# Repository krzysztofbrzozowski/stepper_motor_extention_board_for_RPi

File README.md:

# Stepper motor extention board for Raspberry Pi

Simple extension board for controlling stepper motors (up to 3). Board contains Li-Po battery controller (2-4s). It is also possible to charge battery via USB C. Basic firmware you can find here [stepper_motor_extention_board_firmware.git](https://github.com/krzysztofbrzozowski/stepper_motor_extention_board_firmware.git).
Controller is using simple algorithm for controlling ttepper motors [packets table](https://krzysztofbrzozowski.pl/media/2020/04/05/packet_encoding.png).

Whole project is describerd in polish on my webpage: https://krzysztofbrzozowski.pl/projekt/steronik-silnikow-krokowych-rpi-kontroler-aku-usbc/

## Repository Contents

- **/PCB** - Eagle PCB and schematic files, schematic in PDF

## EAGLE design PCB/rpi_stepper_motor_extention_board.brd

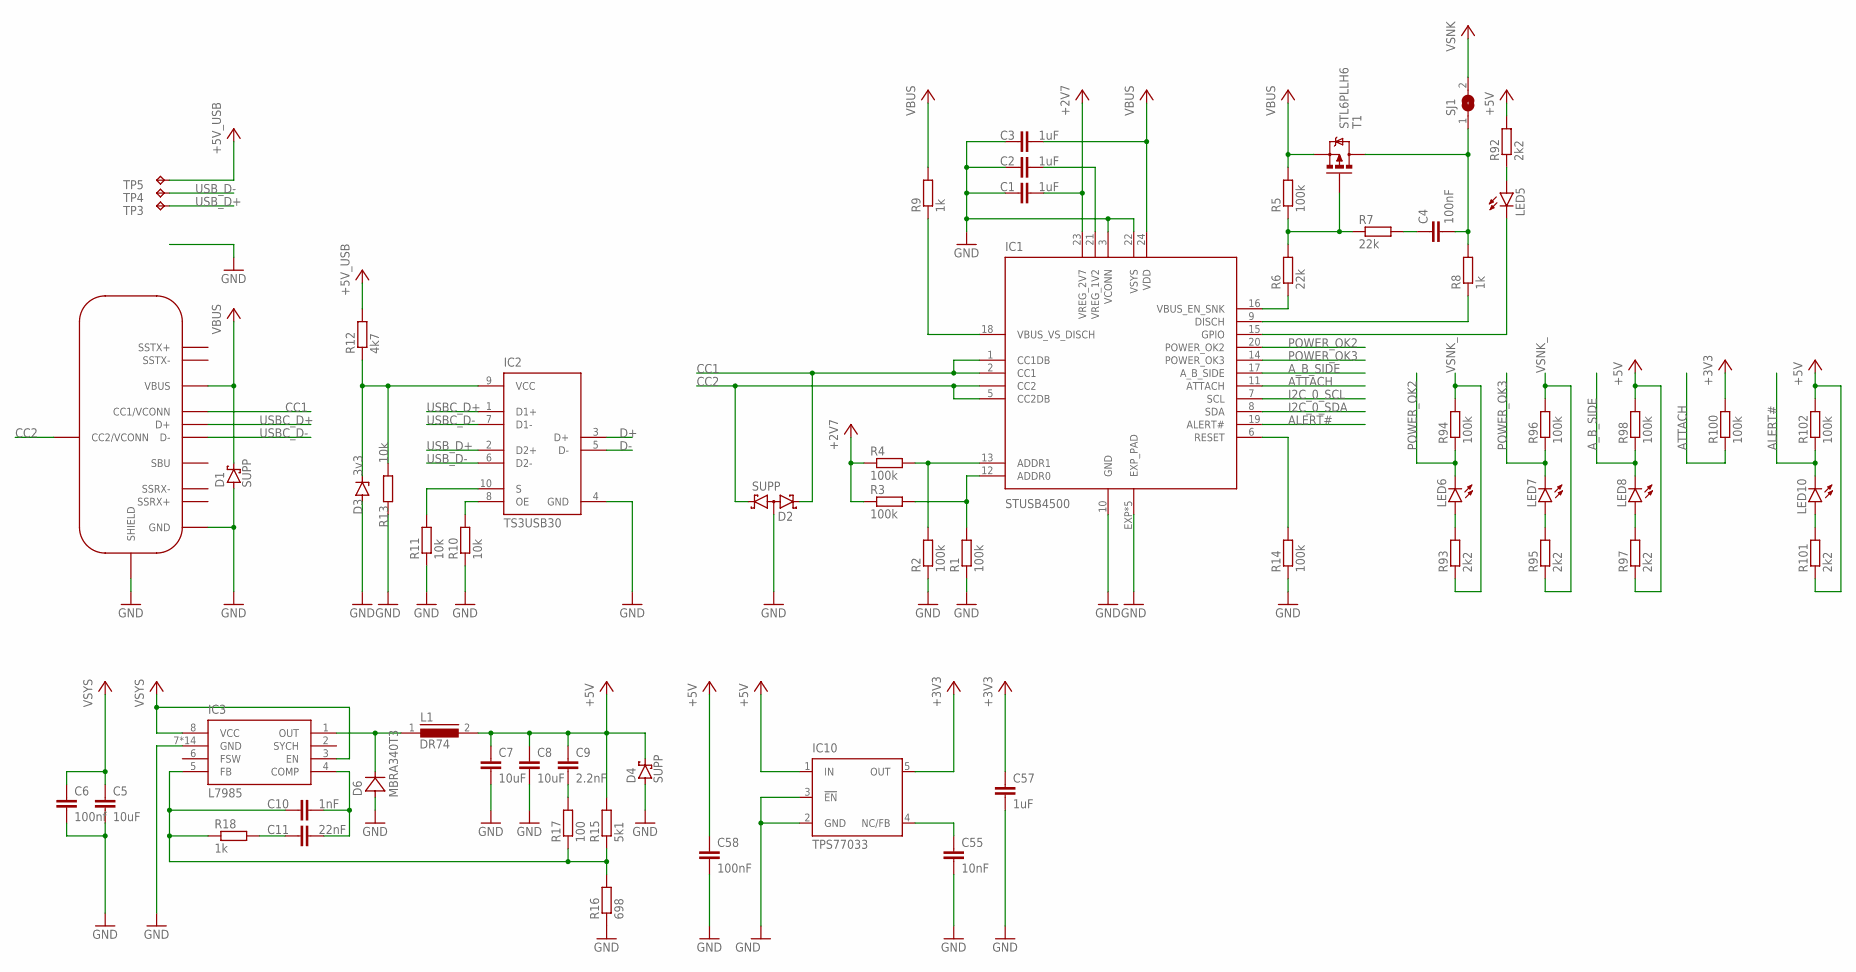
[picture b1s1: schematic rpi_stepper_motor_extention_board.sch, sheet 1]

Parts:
C1, C2, C57: 1uF; C0402K
C3: 1uF; C0603
C4, C58: 100nF; C0402K
C5: 10uF; C1206K
C6: 100nf; C0402K
C7, C8: 10uF; C1210
C9: 2.2nF; C0402K
C10: 1nF; C0402K
C11: 22nF; C0402K
C55: 10nF; C0402K
CON1: USB-TYPE-CHYBRID; USB-TYPE-C-HYBRID
D1, D4: SUPP; SOD123FL
D2: SUPP; SOT23
D3: 3v3; SOD80C
D6: MBRA340T3; SMA
IC1: STUSB4500; QFN50P400X400X90-25T270
IC2: TS3USB30; QFN40P180X145X55-10
IC3: L7985; SOIC127P600X170-8
IC10: TPS77033; SOT23-DBV
L1: DR74
LED5, LED6, LED7, LED8, LED10: LEDCHIPLED_0603; CHIPLED_0603
R1, R2, R3, R4, R5, R14, R94, R96, R98, R100, R102: 100k; R0402
R6, R7: 22k; R0402
R8, R9: 1k; R0603
R10, R11, R13: 10k; R0402
R12: 4k7; R0402
R15: 5k1; R0805
R16: 698; R0805
R17: 100; R0402
R18: 1k; R0402
R92, R93, R95, R97, R101: 2k2; R0402
SJ1: SJ
T1: STL6PLLH6; POWERPAK1212-8
TP3, TP4, TP5: TPB1,27; B1,27

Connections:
+2V7: C1.2, IC1.23 (VREG_2V7), R3.1, R4.1
+3V3: C57.1, IC10.5 (OUT), R100.2; also elsewhere on the board
+5V: C7.1, C8.1, C9.1, C58.1, D4.C, IC10.1 (IN), L1.2, R15.2, R92.2, R97.1, R98.2, R101.1, R102.2; also elsewhere on the board
+5V_USB: R12.2, TP5.TP
ALERT#: IC1.19 (ALERT#), LED10.C, R102.1
ATTACH: IC1.11 (ATTACH), R100.1; also elsewhere on the board
A_B_SIDE: IC1.17 (A_B_SIDE), LED8.C, R98.1
CC1: CON1.5 (CC1/VCONN), D2.2 (K2), IC1.1 (CC1DB), IC1.2 (CC1)
CC2: CON1.B5 (CC2/VCONN), D2.1 (K1), IC1.4 (CC2), IC1.5 (CC2DB)
D+: IC2.3 (D+); also elsewhere on the board
D-: IC2.5 (D-); also elsewhere on the board
GND: C1.1, C2.1, C3.1, C5.2, C6.2, C7.2, C8.2, C55.2, C57.2, C58.2, CON1.1 (GND), CON1.12 (GND), CON1.B1 (GND), CON1.B12 (GND), CON1.P$1 (SHIELD), CON1.P$2 (SHIELD), CON1.P$3 (SHIELD), CON1.P$4 (SHIELD), CON1.P$7 (SHIELD), CON1.P$8 (SHIELD), CON1.P$9 (SHIELD), CON1.P$10 (SHIELD), CON1.P$11 (SHIELD), CON1.P$12 (SHIELD), CON1.P$13 (SHIELD), CON1.P$14 (SHIELD), CON1.P$15 (SHIELD), CON1.P$16 (SHIELD), CON1.P$17 (SHIELD), CON1.P$18 (SHIELD), CON1.P$19 (SHIELD), CON1.P$20 (SHIELD), CON1.P$21 (SHIELD), CON1.P$22 (SHIELD), CON1.P$23 (SHIELD), CON1.P$24 (SHIELD), CON1.P$25 (SHIELD), CON1.P$26 (SHIELD), CON1.P$27 (SHIELD), CON1.P$28 (SHIELD), CON1.P$29 (SHIELD), CON1.P$30 (SHIELD), CON1.P$31 (SHIELD), CON1.P$32 (SHIELD), CON1.P$33 (SHIELD), CON1.P$34 (SHIELD), CON1.P$35 (SHIELD), D1.A, D2.3 (AA), D3.A, D4.A, D6.A, IC1.3 (VCONN), IC1.10 (GND), IC1.22 (VSYS), IC1.EXP (EXP_PAD), IC1.P$1 (EXP_PAD), IC1.P$2 (EXP_PAD), IC1.P$3 (EXP_PAD), IC1.P$4 (EXP_PAD), IC2.4 (GND), IC3.7 (GND), IC3.EXP (GND), IC3.P$1 (GND), IC3.P$2 (GND), IC3.P$3 (GND), IC3.P$4 (GND), IC3.P$5 (GND), IC3.P$6 (GND), IC3.P$7 (GND), IC3.P$8 (GND), IC3.P$9 (GND), IC3.P$10 (GND), IC3.P$11 (GND), IC3.P$12 (GND), IC10.2 (GND), IC10.3 (!EN), R1.1, R2.1, R10.1, R11.1, R13.2, R14.1, R16.1; also elsewhere on the board
I2C_0_SCL: IC1.7 (SCL); also elsewhere on the board
I2C_0_SDA: IC1.8 (SDA); also elsewhere on the board
unnamed: IC1.12 (ADDR0), R1.2, R3.2
unnamed: IC1.13 (ADDR1), R2.2, R4.2
unnamed: C2.2, IC1.21 (VREG_1V2)
unnamed: C4.1, R7.2
unnamed: IC1.16 (VBUS_EN_SNK), R6.1
unnamed: R5.1, R6.2, R7.1, T1.G
unnamed: IC1.18 (VBUS_VS_DISCH), R9.1
unnamed: IC1.9 (DISCH), R8.1
unnamed: IC2.8 (OE), R10.2
unnamed: IC2.10 (S), R11.2
unnamed: D6.C, IC3.1 (OUT), L1.1
unnamed: D3.C, IC2.9 (VCC), R12.1, R13.1
unnamed: IC1.6 (RESET), R14.2
unnamed: C10.1, IC3.5 (FB), R15.1, R16.2, R17.1, R18.1
unnamed: C9.2, R17.2
unnamed: C10.2, C11.2, IC3.4 (COMP)
unnamed: C11.1, R18.2
unnamed: C55.1, IC10.4 (NC/FB)
unnamed: LED5.A, R92.1
unnamed: LED6.A, R93.2
unnamed: LED10.A, R101.2
unnamed: LED7.A, R95.2
unnamed: IC1.15 (GPIO), LED5.C
unnamed: LED8.A, R97.2
POWER_OK2: IC1.20 (POWER_OK2), LED6.C, R94.1
POWER_OK3: IC1.14 (POWER_OK3), LED7.C, R96.1
USBC_D+: CON1.6 (D+), CON1.B6 (D+), IC2.1 (D1+)
USBC_D-: CON1.7 (D-), CON1.B7 (D-), IC2.7 (D1-)
USB_D+: IC2.2 (D2+), TP3.TP
USB_D-: IC2.6 (D2-), TP4.TP
VBUS: C3.2, CON1.4 (VBUS), CON1.9 (VBUS), CON1.B4 (VBUS), CON1.B9 (VBUS), D1.C, IC1.24 (VDD), R5.2, R9.2, T1.S1 (S), T1.S2 (S), T1.S3 (S)
VSNK: SJ1.2; also elsewhere on the board
VSNK_: C4.2, R8.2, R93.1, R94.2, R95.1, R96.2, SJ1.1, T1.D1 (D), T1.D2 (D), T1.D3 (D), T1.D4 (D), T1.DPAD (D)
VSYS: C5.1, C6.1, IC3.3 (EN), IC3.8 (VCC); also elsewhere on the board

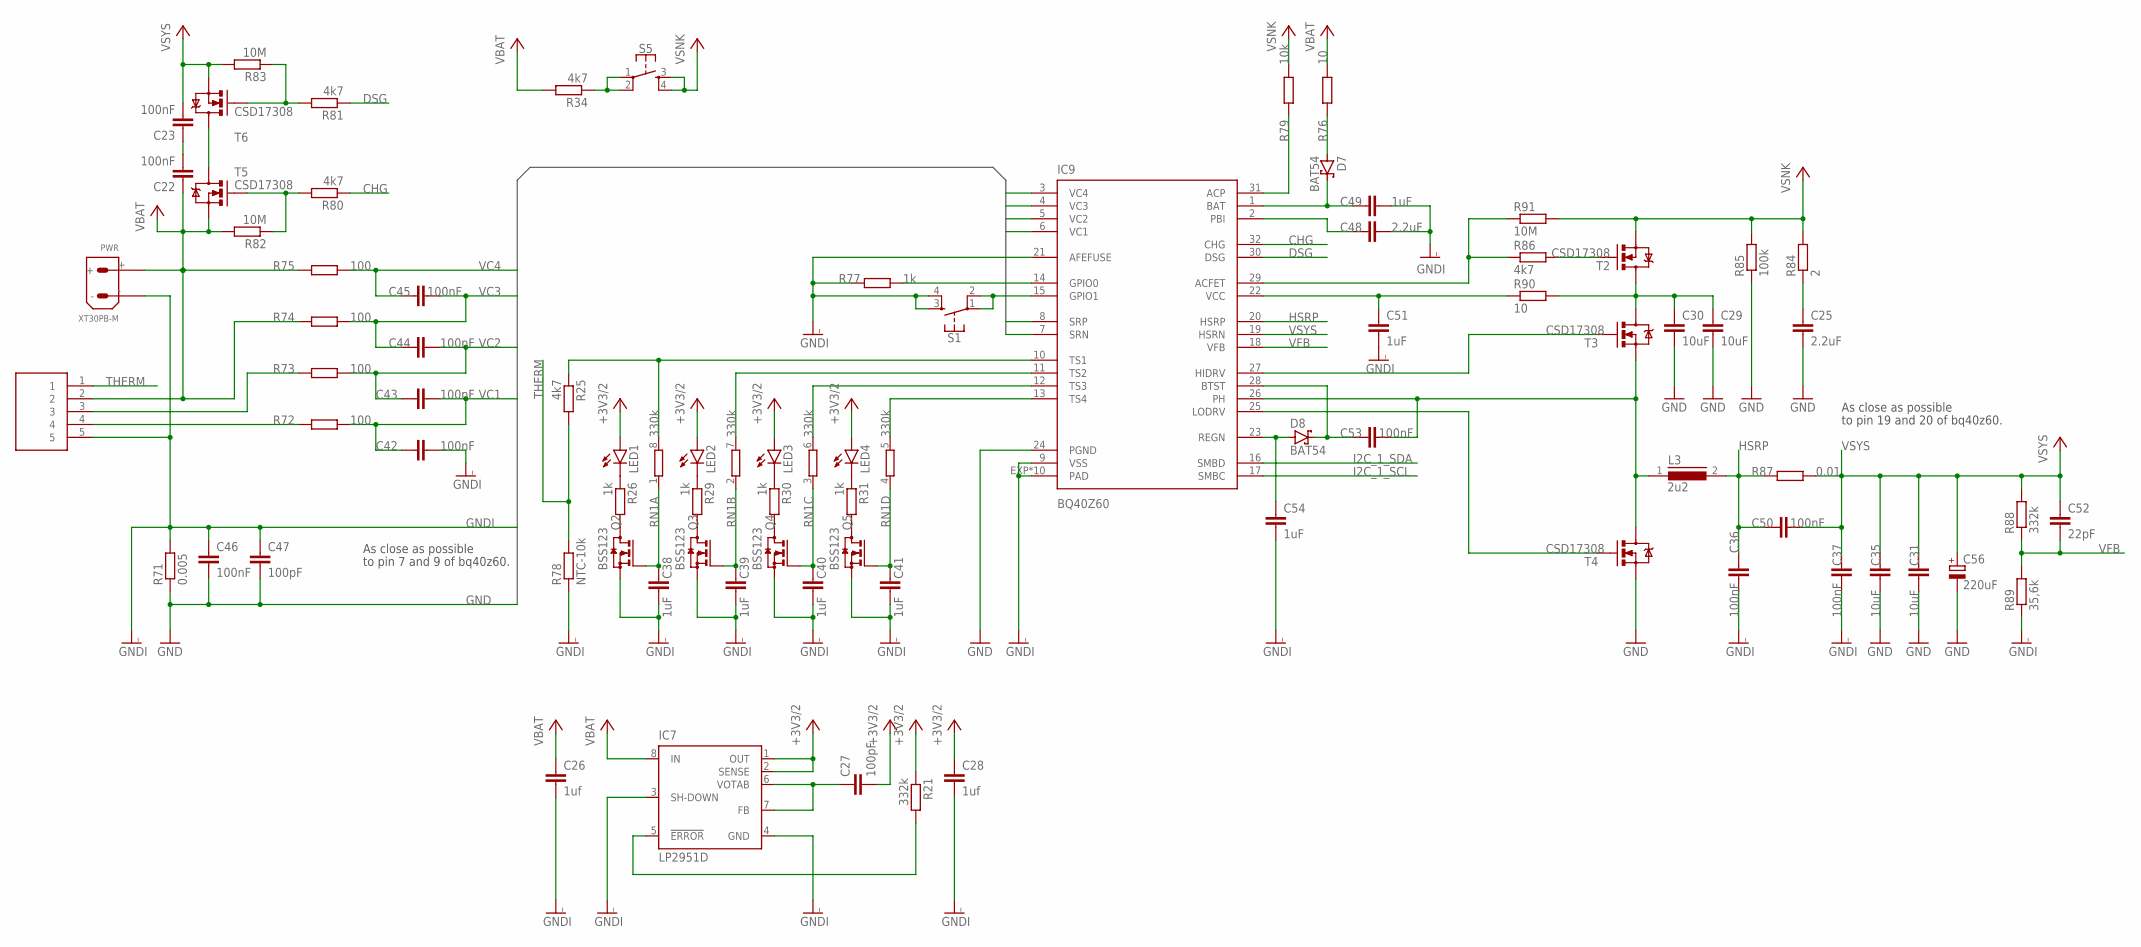
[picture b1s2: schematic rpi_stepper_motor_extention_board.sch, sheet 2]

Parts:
C22, C23: 100nF; C0603K
C25, C48: 2.2uF; C0603K
C26, C28: 1uf; C0402
C27, C47: 100pF; C0402
C29, C30, C31, C35: 10uF; C1206K
C36, C37, C42, C43, C44, C45, C50, C53: 100nF; C0402K
C38, C39, C40, C41: 1uF; C0402K
C46: 100nF; C0402
C49, C51, C54: 1uF; C0603K
C52: 22pF; C0402K
C56: 220uF; 153CLV-0605
D7, D8: BAT54; SOD123FL
IC7: LP2951D; SO08
IC9: BQ40Z60; QFN50P500X500X100-33T345
L3: 2u2; DR74
LED1, LED2, LED3, LED4: LEDCHIPLED_0603; CHIPLED_0603
PWR: XT30PB-M
Q2, Q3, Q4, Q5: BSS123; SOT23
R21: 332k; R0402
R25, R34, R80, R81, R86: 4k7; R0402
R26, R29, R30, R31, R77: 1k; R0402
R71: 0.005; R2010
R72, R73, R74, R75: 100; R0603
R76: 10; R0402
R78: NTC-10k; R0603
R79: 10k; R0402
R82, R83, R91: 10M; R0402
R84: 2; R0603
R85: 100k; R0402
R87: 0.01; R2512
R88: 332k; R0805
R89: 35,6k; R0805
R90: 10; R1206
RN1: 330k; 0603-ARC
S1, S5: MOMENTARY-SWITCH-SPST-2-SMD-4.6X2.8MM; TACTILE_SWITCH_SMD_4.6X2.8MM
T2, T3, T4, T5, T6: CSD17308; POWERPAK1212-8
U$1: 5PIN_CON_JOINT_TECH

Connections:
+3V3/2: C27.2, C28.1, IC7.1 (OUT), IC7.2 (SENSE), LED1.A, LED2.A, LED3.A, LED4.A, R21.1
CHG: IC9.32 (CHG), R80.1
DSG: IC9.30 (DSG), R81.1
GND: C25.2, C29.2, C30.2, C31.2, C35.2, C46.2, C47.2, C56.-, IC9.7 (SRN), IC9.24 (PGND), R71.1, R85.1, T4.S1 (S), T4.S2 (S), T4.S3 (S); also elsewhere on the board
GNDI: C26.2, C28.2, C36.2, C37.2, C38.2, C39.2, C40.2, C41.2, C42.1, C46.1, C47.1, C48.2, C49.2, C51.2, C54.2, IC7.3 (SH-DOWN), IC7.4 (GND), IC9.8 (SRP), IC9.9 (VSS), IC9.21 (AFEFUSE), IC9.EXP (PAD), IC9.P$1 (PAD), IC9.P$2 (PAD), IC9.P$3 (PAD), IC9.P$4 (PAD), IC9.P$5 (PAD), IC9.P$6 (PAD), IC9.P$7 (PAD), IC9.P$8 (PAD), IC9.P$9 (PAD), PWR.-, Q2.2 (S), Q3.2 (S), Q4.2 (S), Q5.2 (S), R71.2, R77.1, R78.1, R89.1, S1.3, S1.4, U$1.5
HSRP: C36.1, C50.1, IC9.20 (HSRP), L3.2, R87.1
I2C_1_SCL: IC9.17 (SMBC); also elsewhere on the board
I2C_1_SDA: IC9.16 (SMBD); also elsewhere on the board
unnamed: LED1.C, R26.1
unnamed: LED2.C, R29.1
unnamed: LED3.C, R30.1
unnamed: LED4.C, R31.1
unnamed: C27.1, IC7.6 (VOTAB), IC7.7 (FB)
unnamed: Q2.3 (D), R26.2
unnamed: Q3.3 (D), R29.2
unnamed: IC7.5 (!ERROR), R21.2
unnamed: Q5.3 (D), R31.2
unnamed: Q4.3 (D), R30.2
unnamed: R34.1, S5.1, S5.2
unnamed: C38.1, Q2.1 (G), RN1.1
unnamed: C48.1, IC9.2 (PBI)
unnamed: IC9.10 (TS1), R25.1, RN1.8 (2)
unnamed: IC9.11 (TS2), RN1.7 (2)
unnamed: IC9.12 (TS3), RN1.6 (2)
unnamed: IC9.13 (TS4), RN1.5 (2)
unnamed: C39.1, Q3.1 (G), RN1.2 (1)
unnamed: D7.A, R76.1
unnamed: R72.1, U$1.4
unnamed: C40.1, Q4.1 (G), RN1.3 (1)
unnamed: C41.1, Q5.1 (G), RN1.4 (1)
unnamed: C49.1, D7.C, IC9.1 (BAT)
unnamed: R73.1, U$1.3
unnamed: IC9.14 (GPIO0), R77.2
unnamed: IC9.15 (GPIO1), S1.1, S1.2
unnamed: IC9.31 (ACP), R79.1
unnamed: T5.D1 (D), T5.D2 (D), T5.D3 (D), T5.D4 (D), T5.DPAD (D), T6.D1 (D), T6.D2 (D), T6.D3 (D), T6.D4 (D), T6.DPAD (D)
unnamed: R80.2, R82.1, T5.G
unnamed: R81.2, R83.1, T6.G
unnamed: C25.1, R84.1
unnamed: C22.2, C23.1
unnamed: C29.1, C30.1, R90.2, T2.D1 (D), T2.D2 (D), T2.D3 (D), T2.D4 (D), T2.DPAD (D), T3.D1 (D), T3.D2 (D), T3.D3 (D), T3.D4 (D), T3.DPAD (D)
unnamed: C53.2, IC9.26 (PH), L3.1, T3.S1 (S), T3.S2 (S), T3.S3 (S), T4.D1 (D), T4.D2 (D), T4.D3 (D), T4.D4 (D), T4.DPAD (D)
unnamed: R86.2, T2.G
unnamed: IC9.27 (HIDRV), T3.G
unnamed: IC9.25 (LODRV), T4.G
unnamed: IC9.29 (ACFET), R86.1, R91.1
unnamed: C51.1, IC9.22 (VCC), R90.1
unnamed: C54.1, D8.A, IC9.23 (REGN)
unnamed: C53.1, D8.C, IC9.28 (BTST)
THERM: R25.2, R78.2, U$1.1
VBAT: C22.1, C26.1, IC7.8 (IN), PWR.+, R34.2, R74.1, R75.1, R76.2, R82.2, T5.S1 (S), T5.S2 (S), T5.S3 (S), U$1.2
VC1: C42.2, C43.1, IC9.6 (VC1), R72.2
VC2: C43.2, C44.1, IC9.5 (VC2), R73.2
VC3: C44.2, C45.1, IC9.4 (VC3), R74.2
VC4: C45.2, IC9.3 (VC4), R75.2
VFB: C52.2, IC9.18 (VFB), R88.1, R89.2
VSNK: R79.2, R84.2, R85.2, R91.2, S5.3, S5.4, T2.S1 (S), T2.S2 (S), T2.S3 (S); also elsewhere on the board
VSYS: C23.2, C31.1, C35.1, C37.1, C50.2, C52.1, C56.+, IC9.19 (HSRN), R83.2, R87.2, R88.2, T6.S1 (S), T6.S2 (S), T6.S3 (S); also elsewhere on the board

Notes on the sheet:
As close as possible
to pin 7 and 9 of bq40z60.
to pin 19 and 20 of bq40z60.

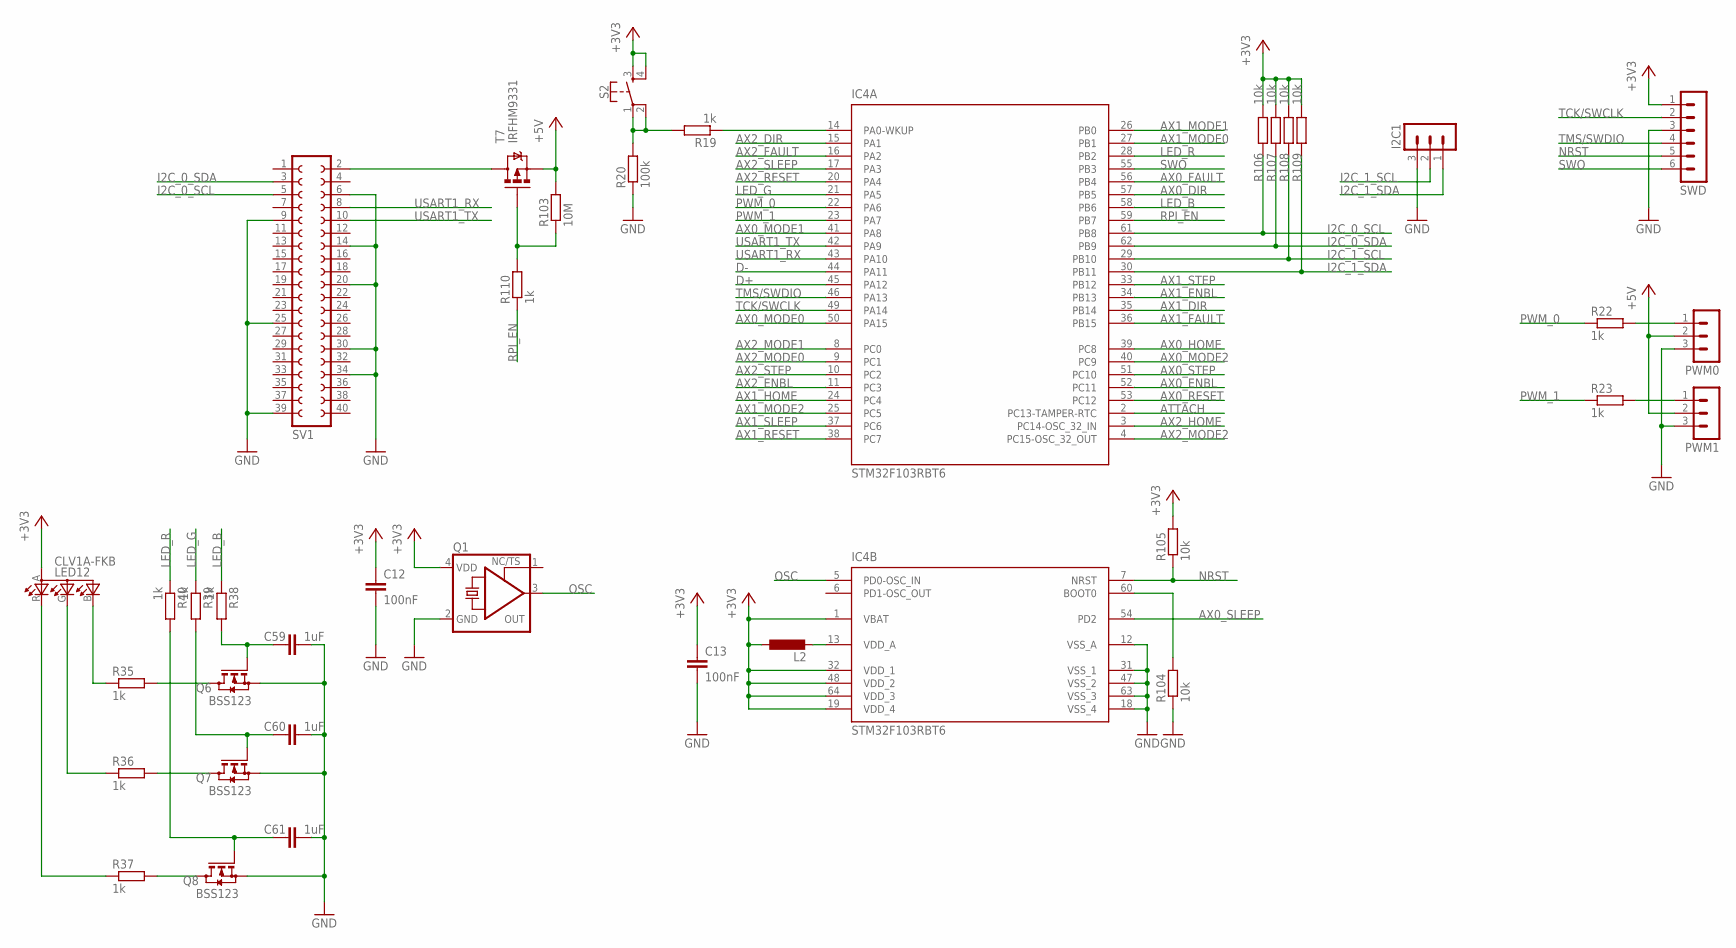
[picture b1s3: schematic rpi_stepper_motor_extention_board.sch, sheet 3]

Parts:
C12, C13: 100nF; C0402K
C59, C60, C61: 1uF; C0402K
I2C1: MA03-1
IC4: STM32F103RBT6; QFP50P1200X1200X160-64
L2: L-EUL2012C; L2012C
LED12: CLV1A-FKB
PWM0, PWM1: MA03-1
Q1: KXO-PXO/XO-V95; 2.5X2.0_KXO-V95
Q6, Q7, Q8: BSS123; SOT23
R19, R22, R23, R35, R36, R37, R38, R39, R40, R110: 1k; R0402
R20: 100k; R0402
R103: 10M; R0402
R104, R105, R106, R107, R108, R109: 10k; R0402
S2: MOMENTARY-SWITCH-SPST-2-SMD-4.6X2.8MM; TACTILE_SWITCH_SMD_4.6X2.8MM
SV1: FE20-2
SWD: MA06-1
T7: IRFHM9331; POWERPAK1212-8

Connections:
+3V3: C12.1, C13.1, IC4.1 (VBAT), IC4.19 (VDD_4), IC4.32 (VDD_1), IC4.48 (VDD_2), IC4.64 (VDD_3), L2.1, LED12.A (ANODE), Q1.4 (VDD), R105.2, R106.2, R107.2, R108.2, R109.2, S2.3, S2.4, SWD.1; also elsewhere on the board
+5V: PWM0.2, PWM1.2, R103.2, T7.S1 (S), T7.S2 (S), T7.S3 (S); also elsewhere on the board
ATTACH: IC4.2 (PC13-TAMPER-RTC); also elsewhere on the board
AX0_DIR: IC4.57 (PB5); also elsewhere on the board
AX0_ENBL: IC4.52 (PC11); also elsewhere on the board
AX0_FAULT: IC4.56 (PB4); also elsewhere on the board
AX0_HOME: IC4.39 (PC8); also elsewhere on the board
AX0_MODE0: IC4.50 (PA15); also elsewhere on the board
AX0_MODE1: IC4.41 (PA8); also elsewhere on the board
AX0_MODE2: IC4.40 (PC9); also elsewhere on the board
AX0_RESET: IC4.53 (PC12); also elsewhere on the board
AX0_SLEEP: IC4.54 (PD2); also elsewhere on the board
AX0_STEP: IC4.51 (PC10); also elsewhere on the board
AX1_DIR: IC4.35 (PB14); also elsewhere on the board
AX1_ENBL: IC4.34 (PB13); also elsewhere on the board
AX1_FAULT: IC4.36 (PB15); also elsewhere on the board
AX1_HOME: IC4.24 (PC4); also elsewhere on the board
AX1_MODE0: IC4.27 (PB1); also elsewhere on the board
AX1_MODE1: IC4.26 (PB0); also elsewhere on the board
AX1_MODE2: IC4.25 (PC5); also elsewhere on the board
AX1_RESET: IC4.38 (PC7); also elsewhere on the board
AX1_SLEEP: IC4.37 (PC6); also elsewhere on the board
AX1_STEP: IC4.33 (PB12); also elsewhere on the board
AX2_DIR: IC4.15 (PA1); also elsewhere on the board
AX2_ENBL: IC4.11 (PC3); also elsewhere on the board
AX2_FAULT: IC4.16 (PA2); also elsewhere on the board
AX2_HOME: IC4.3 (PC14-OSC_32_IN); also elsewhere on the board
AX2_MODE0: IC4.9 (PC1); also elsewhere on the board
AX2_MODE1: IC4.8 (PC0); also elsewhere on the board
AX2_MODE2: IC4.4 (PC15-OSC_32_OUT); also elsewhere on the board
AX2_RESET: IC4.20 (PA4); also elsewhere on the board
AX2_SLEEP: IC4.17 (PA3); also elsewhere on the board
AX2_STEP: IC4.10 (PC2); also elsewhere on the board
D+: IC4.45 (PA12); also elsewhere on the board
D-: IC4.44 (PA11); also elsewhere on the board
GND: C12.2, C13.2, C59.2, C60.2, C61.2, I2C1.3, IC4.12 (VSS_A), IC4.18 (VSS_4), IC4.31 (VSS_1), IC4.47 (VSS_2), IC4.63 (VSS_3), PWM0.3, PWM1.3, Q1.2 (GND), Q6.2 (S), Q7.2 (S), Q8.2 (S), R20.1, R104.1, SV1.6, SV1.9, SV1.14, SV1.20, SV1.25, SV1.30, SV1.34, SV1.39, SWD.3; also elsewhere on the board
I2C_0_SCL: IC4.61 (PB8), R106.1, SV1.5; also elsewhere on the board
I2C_0_SDA: IC4.62 (PB9), R107.1, SV1.3; also elsewhere on the board
I2C_1_SCL: I2C1.2, IC4.29 (PB10), R108.1; also elsewhere on the board
I2C_1_SDA: I2C1.1, IC4.30 (PB11), R109.1; also elsewhere on the board
LED_B: IC4.58 (PB6), R38.1
LED_G: IC4.21 (PA5), R39.1
LED_R: IC4.28 (PB2), R40.1
unnamed: IC4.13 (VDD_A), L2.2
unnamed: LED12.G (CGREEN), R36.1
unnamed: C59.1, Q6.1 (G), R38.2
unnamed: IC4.14 (PA0-WKUP), R19.1
unnamed: LED12.R (CRED), R37.1
unnamed: LED12.B (CBLUE), R35.1
unnamed: Q8.3 (D), R37.2
unnamed: Q7.3 (D), R36.2
unnamed: Q6.3 (D), R35.2
unnamed: C60.1, Q7.1 (G), R39.2
unnamed: C61.1, Q8.1 (G), R40.2
unnamed: SV1.2, T7.D1 (D), T7.D2 (D), T7.D3 (D), T7.D4 (D), T7.DPAD (D)
unnamed: IC4.60 (BOOT0), R104.2
unnamed: R103.1, R110.2, T7.G
unnamed: R19.2, R20.2, S2.1, S2.2
unnamed: PWM0.1, R22.2
unnamed: PWM1.1, R23.2
NRST: IC4.7 (NRST), R105.1, SWD.5
OSC: IC4.5 (PD0-OSC_IN), Q1.3 (OUT)
PWM_0: IC4.22 (PA6), R22.1
PWM_1: IC4.23 (PA7), R23.1
RPI_EN: IC4.59 (PB7), R110.1
SWO: IC4.55 (PB3), SWD.6
TCK/SWCLK: IC4.49 (PA14), SWD.2
TMS/SWDIO: IC4.46 (PA13), SWD.4
USART1_RX: IC4.43 (PA10), SV1.8
USART1_TX: IC4.42 (PA9), SV1.10

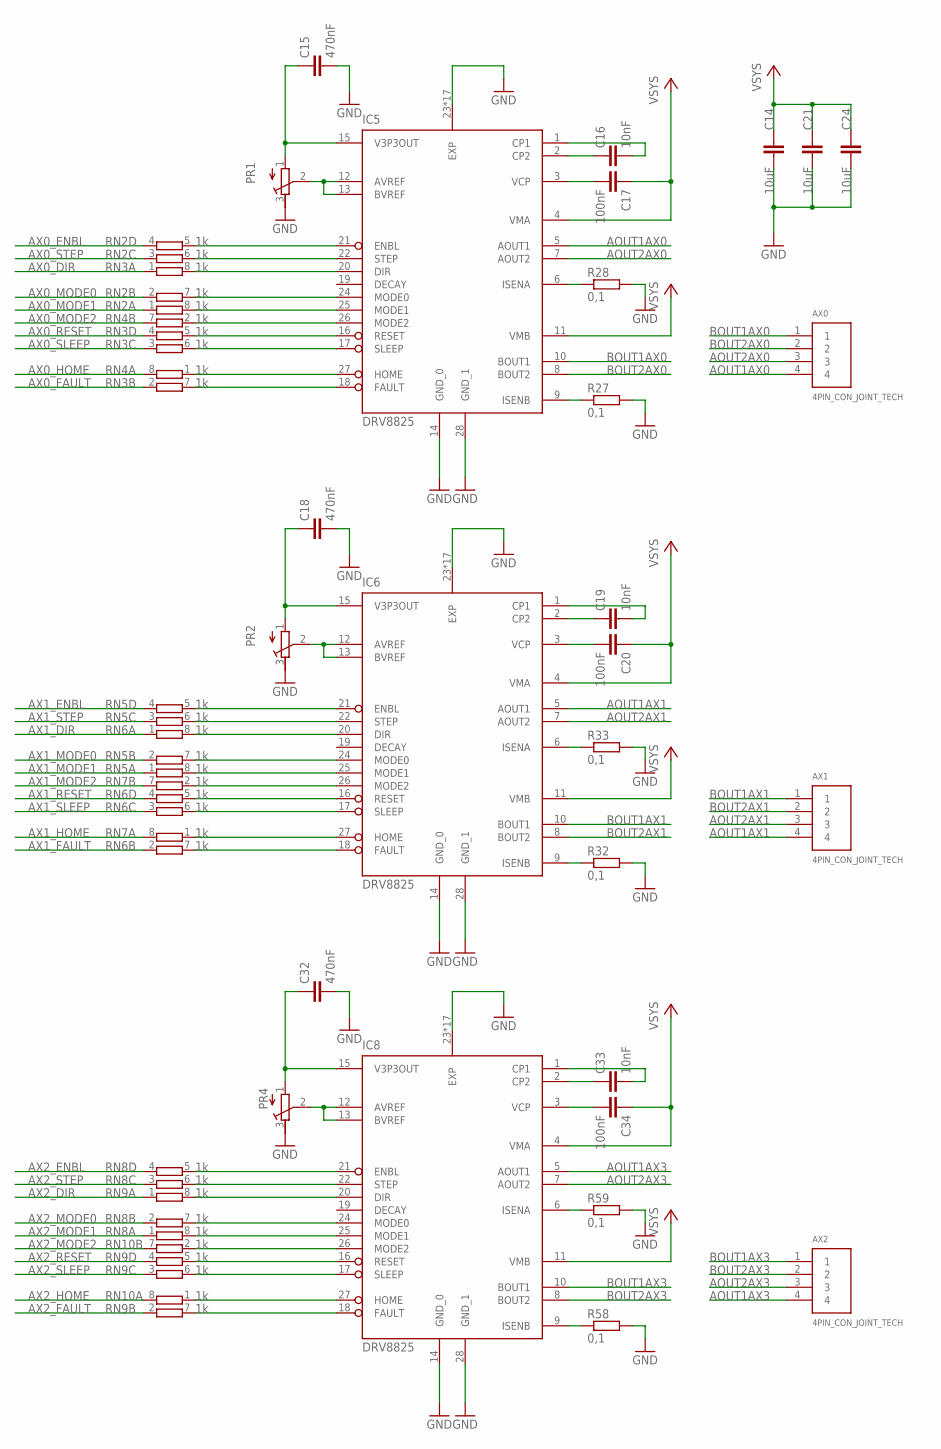
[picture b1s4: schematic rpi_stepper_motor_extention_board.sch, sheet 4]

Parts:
AX0, AX1, AX2: 4PIN_CON_JOINT_TECH
C14, C21, C24: 10uF; C1206K
C15, C18, C32: 470nF; C0402K
C16, C19, C33: 10nF; C0402K
C17, C20, C34: 100nF; C0402K
IC5, IC6, IC8: DRV8825; SOP65P640X120-28
PR1, PR2, PR4: R-TRIMM3224J; RTRIM3224J
R27, R28, R32, R33, R58, R59: 0,1; R0805
RN2, RN3, RN4, RN5, RN6, RN7, RN8, RN9, RN10: 1k; 0603-ARC

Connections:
AOUT1AX0: AX0.4, IC5.5 (AOUT1)
AOUT1AX1: AX1.4, IC6.5 (AOUT1)
AOUT1AX3: AX2.4, IC8.5 (AOUT1)
AOUT2AX0: AX0.3, IC5.7 (AOUT2)
AOUT2AX1: AX1.3, IC6.7 (AOUT2)
AOUT2AX3: AX2.3, IC8.7 (AOUT2)
AX0_DIR: RN3.1; also elsewhere on the board
AX0_ENBL: RN2.4 (1); also elsewhere on the board
AX0_FAULT: RN3.2 (1); also elsewhere on the board
AX0_HOME: RN4.8 (2); also elsewhere on the board
AX0_MODE0: RN2.2 (1); also elsewhere on the board
AX0_MODE1: RN2.1; also elsewhere on the board
AX0_MODE2: RN4.7 (2); also elsewhere on the board
AX0_RESET: RN3.4 (1); also elsewhere on the board
AX0_SLEEP: RN3.3 (1); also elsewhere on the board
AX0_STEP: RN2.3 (1); also elsewhere on the board
AX1_DIR: RN6.1; also elsewhere on the board
AX1_ENBL: RN5.4 (1); also elsewhere on the board
AX1_FAULT: RN6.2 (1); also elsewhere on the board
AX1_HOME: RN7.8 (2); also elsewhere on the board
AX1_MODE0: RN5.2 (1); also elsewhere on the board
AX1_MODE1: RN5.1; also elsewhere on the board
AX1_MODE2: RN7.7 (2); also elsewhere on the board
AX1_RESET: RN6.4 (1); also elsewhere on the board
AX1_SLEEP: RN6.3 (1); also elsewhere on the board
AX1_STEP: RN5.3 (1); also elsewhere on the board
AX2_DIR: RN9.1; also elsewhere on the board
AX2_ENBL: RN8.4 (1); also elsewhere on the board
AX2_FAULT: RN9.2 (1); also elsewhere on the board
AX2_HOME: RN10.8 (2); also elsewhere on the board
AX2_MODE0: RN8.2 (1); also elsewhere on the board
AX2_MODE1: RN8.1; also elsewhere on the board
AX2_MODE2: RN10.7 (2); also elsewhere on the board
AX2_RESET: RN9.4 (1); also elsewhere on the board
AX2_SLEEP: RN9.3 (1); also elsewhere on the board
AX2_STEP: RN8.3 (1); also elsewhere on the board
BOUT1AX0: AX0.1, IC5.10 (BOUT1)
BOUT1AX1: AX1.1, IC6.10 (BOUT1)
BOUT1AX3: AX2.1, IC8.10 (BOUT1)
BOUT2AX0: AX0.2, IC5.8 (BOUT2)
BOUT2AX1: AX1.2, IC6.8 (BOUT2)
BOUT2AX3: AX2.2, IC8.8 (BOUT2)
GND: C14.2, C15.2, C18.2, C21.2, C24.2, C32.2, IC5.14 (GND_0), IC5.23 (EXP), IC5.28 (GND_1), IC5.EXP, IC5.P$1 (EXP), IC5.P$2 (EXP), IC5.P$3 (EXP), IC5.P$4 (EXP), IC5.P$5 (EXP), IC5.P$6 (EXP), IC5.P$7 (EXP), IC5.P$8 (EXP), IC5.P$9 (EXP), IC5.P$10 (EXP), IC5.P$11 (EXP), IC5.P$12 (EXP), IC5.P$13 (EXP), IC5.P$14 (EXP), IC5.P$15 (EXP), IC6.14 (GND_0), IC6.23 (EXP), IC6.28 (GND_1), IC6.EXP, IC6.P$1 (EXP), IC6.P$2 (EXP), IC6.P$3 (EXP), IC6.P$4 (EXP), IC6.P$5 (EXP), IC6.P$6 (EXP), IC6.P$7 (EXP), IC6.P$8 (EXP), IC6.P$9 (EXP), IC6.P$10 (EXP), IC6.P$11 (EXP), IC6.P$12 (EXP), IC6.P$13 (EXP), IC6.P$14 (EXP), IC6.P$15 (EXP), IC8.14 (GND_0), IC8.23 (EXP), IC8.28 (GND_1), IC8.EXP, IC8.P$1 (EXP), IC8.P$2 (EXP), IC8.P$3 (EXP), IC8.P$4 (EXP), IC8.P$5 (EXP), IC8.P$6 (EXP), IC8.P$7 (EXP), IC8.P$8 (EXP), IC8.P$9 (EXP), IC8.P$10 (EXP), IC8.P$11 (EXP), IC8.P$12 (EXP), IC8.P$13 (EXP), IC8.P$14 (EXP), IC8.P$15 (EXP), PR1.3 (E), PR2.3 (E), PR4.3 (E), R27.2, R28.2, R32.2, R33.2, R58.2, R59.2; also elsewhere on the board
unnamed: IC5.21 (ENBL), RN2.5 (2)
unnamed: IC5.22 (STEP), RN2.6 (2)
unnamed: IC5.20 (DIR), RN3.8 (2)
unnamed: IC5.16 (RESET), RN3.5 (2)
unnamed: IC5.18 (FAULT), RN3.7 (2)
unnamed: IC5.24 (MODE0), RN2.7 (2)
unnamed: IC5.12 (AVREF), IC5.13 (BVREF), PR1.2 (S)
unnamed: IC5.25 (MODE1), RN2.8 (2)
unnamed: C15.1, IC5.15 (V3P3OUT), PR1.1 (A)
unnamed: IC5.17 (SLEEP), RN3.6 (2)
unnamed: C16.1, IC5.2 (CP2)
unnamed: C16.2, IC5.1 (CP1)
unnamed: IC5.9 (ISENB), R27.1
unnamed: IC5.6 (ISENA), R28.1
unnamed: C17.2, IC5.3 (VCP)
unnamed: IC5.26 (MODE2), RN4.2 (1)
unnamed: IC6.12 (AVREF), IC6.13 (BVREF), PR2.2 (S)
unnamed: C18.1, IC6.15 (V3P3OUT), PR2.1 (A)
unnamed: IC6.17 (SLEEP), RN6.6 (2)
unnamed: C19.1, IC6.2 (CP2)
unnamed: C19.2, IC6.1 (CP1)
unnamed: IC6.9 (ISENB), R32.1
unnamed: IC6.6 (ISENA), R33.1
unnamed: C20.2, IC6.3 (VCP)
unnamed: IC6.21 (ENBL), RN5.5 (2)
unnamed: IC6.22 (STEP), RN5.6 (2)
unnamed: IC6.20 (DIR), RN6.8 (2)
unnamed: IC6.16 (RESET), RN6.5 (2)
unnamed: IC6.18 (FAULT), RN6.7 (2)
unnamed: IC6.24 (MODE0), RN5.7 (2)
unnamed: IC6.25 (MODE1), RN5.8 (2)
unnamed: IC6.26 (MODE2), RN7.2 (1)
unnamed: IC5.27 (HOME), RN4.1
unnamed: IC8.27 (HOME), RN10.1
unnamed: IC6.27 (HOME), RN7.1
unnamed: IC8.12 (AVREF), IC8.13 (BVREF), PR4.2 (S)
unnamed: C32.1, IC8.15 (V3P3OUT), PR4.1 (A)
unnamed: IC8.17 (SLEEP), RN9.6 (2)
unnamed: C33.1, IC8.2 (CP2)
unnamed: C33.2, IC8.1 (CP1)
unnamed: IC8.9 (ISENB), R58.1
unnamed: IC8.6 (ISENA), R59.1
unnamed: C34.2, IC8.3 (VCP)
unnamed: IC8.21 (ENBL), RN8.5 (2)
unnamed: IC8.22 (STEP), RN8.6 (2)
unnamed: IC8.20 (DIR), RN9.8 (2)
unnamed: IC8.16 (RESET), RN9.5 (2)
unnamed: IC8.18 (FAULT), RN9.7 (2)
unnamed: IC8.24 (MODE0), RN8.7 (2)
unnamed: IC8.25 (MODE1), RN8.8 (2)
unnamed: IC8.26 (MODE2), RN10.2 (1)
VSYS: C14.1, C17.1, C20.1, C21.1, C24.1, C34.1, IC5.4 (VMA), IC5.11 (VMB), IC6.4 (VMA), IC6.11 (VMB), IC8.4 (VMA), IC8.11 (VMB); also elsewhere on the board

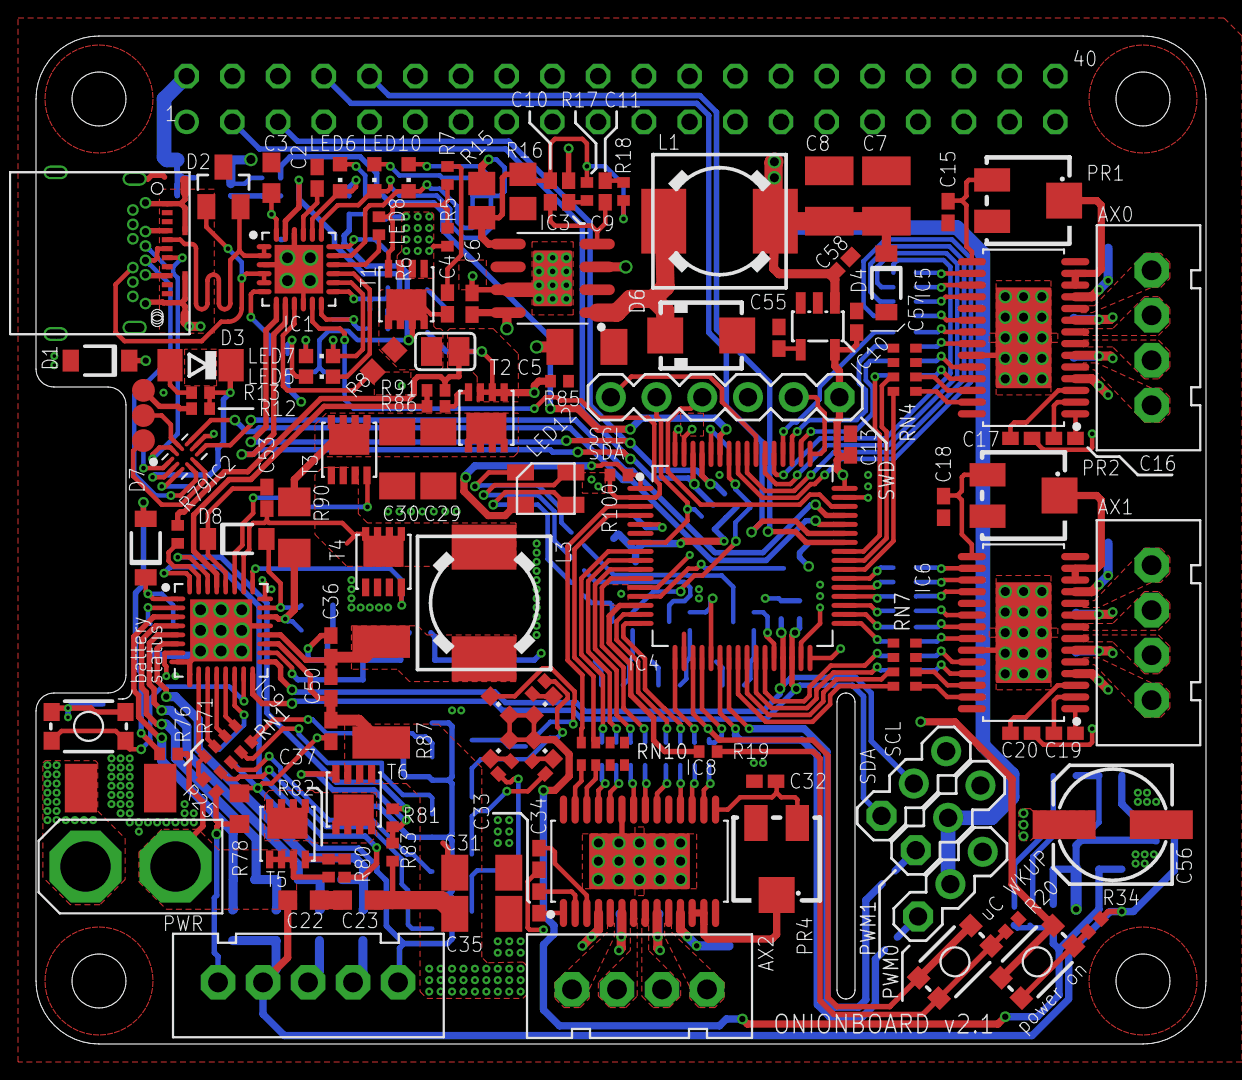
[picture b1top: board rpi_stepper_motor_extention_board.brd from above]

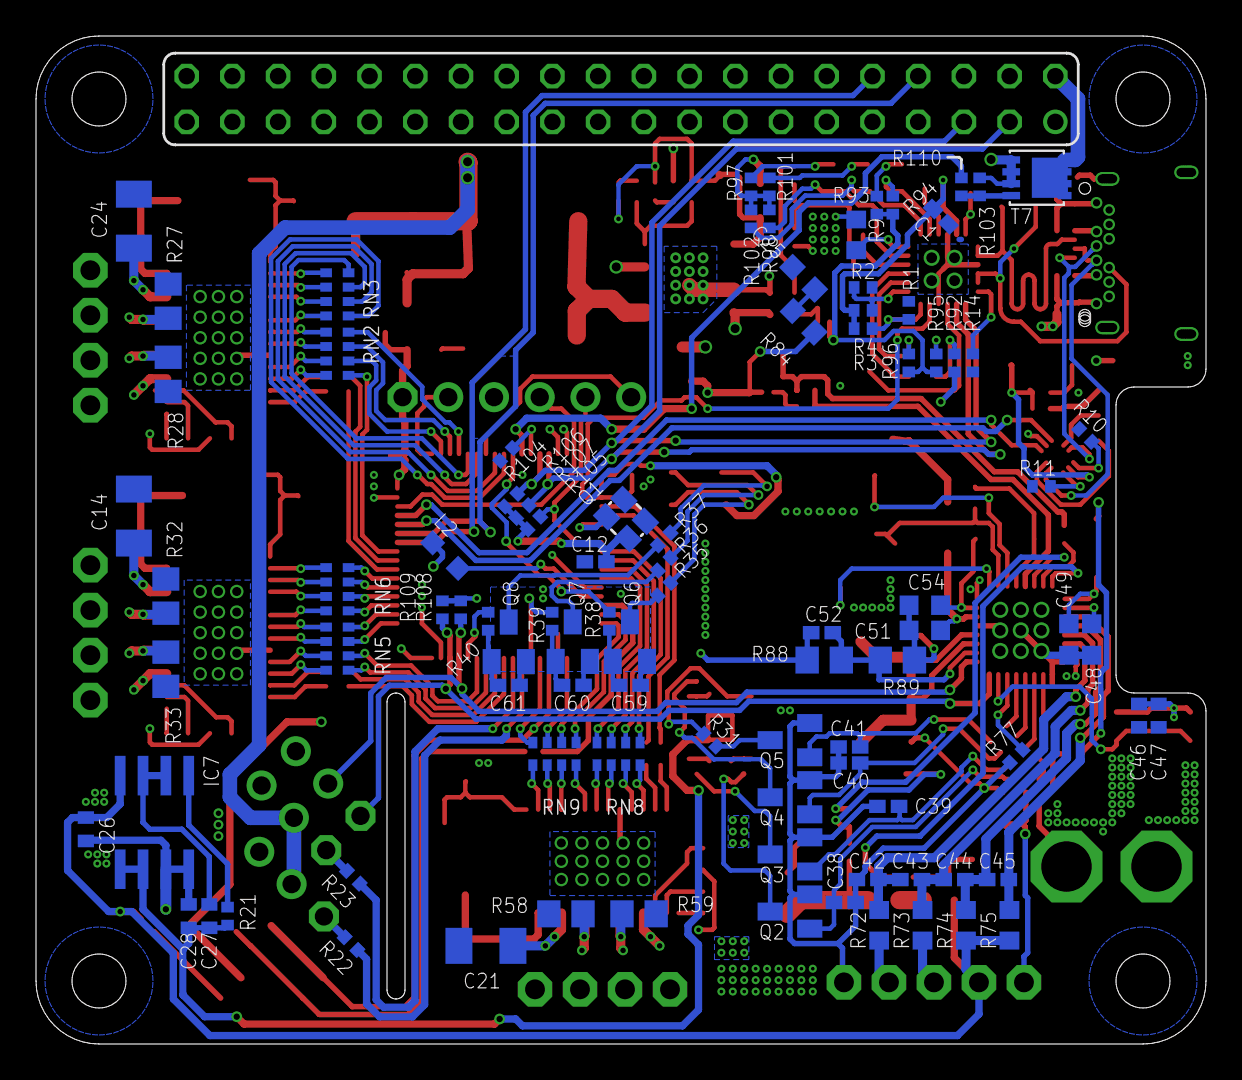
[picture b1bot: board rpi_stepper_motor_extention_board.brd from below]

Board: 4 copper layers, 65.0 x 56.0 mm, 217 parts (94 on the bottom side), 226 nets.

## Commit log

2020-04-05 typo fix

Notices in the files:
parts and their libraries:
crystal-geyer_V1_0: Copyright: Geyer-Electronic
SparkFun-Switches: Licensing: Creative Commons ShareAlike 4.0 International - https://creativecommons.org/licenses/by-sa/4.0
